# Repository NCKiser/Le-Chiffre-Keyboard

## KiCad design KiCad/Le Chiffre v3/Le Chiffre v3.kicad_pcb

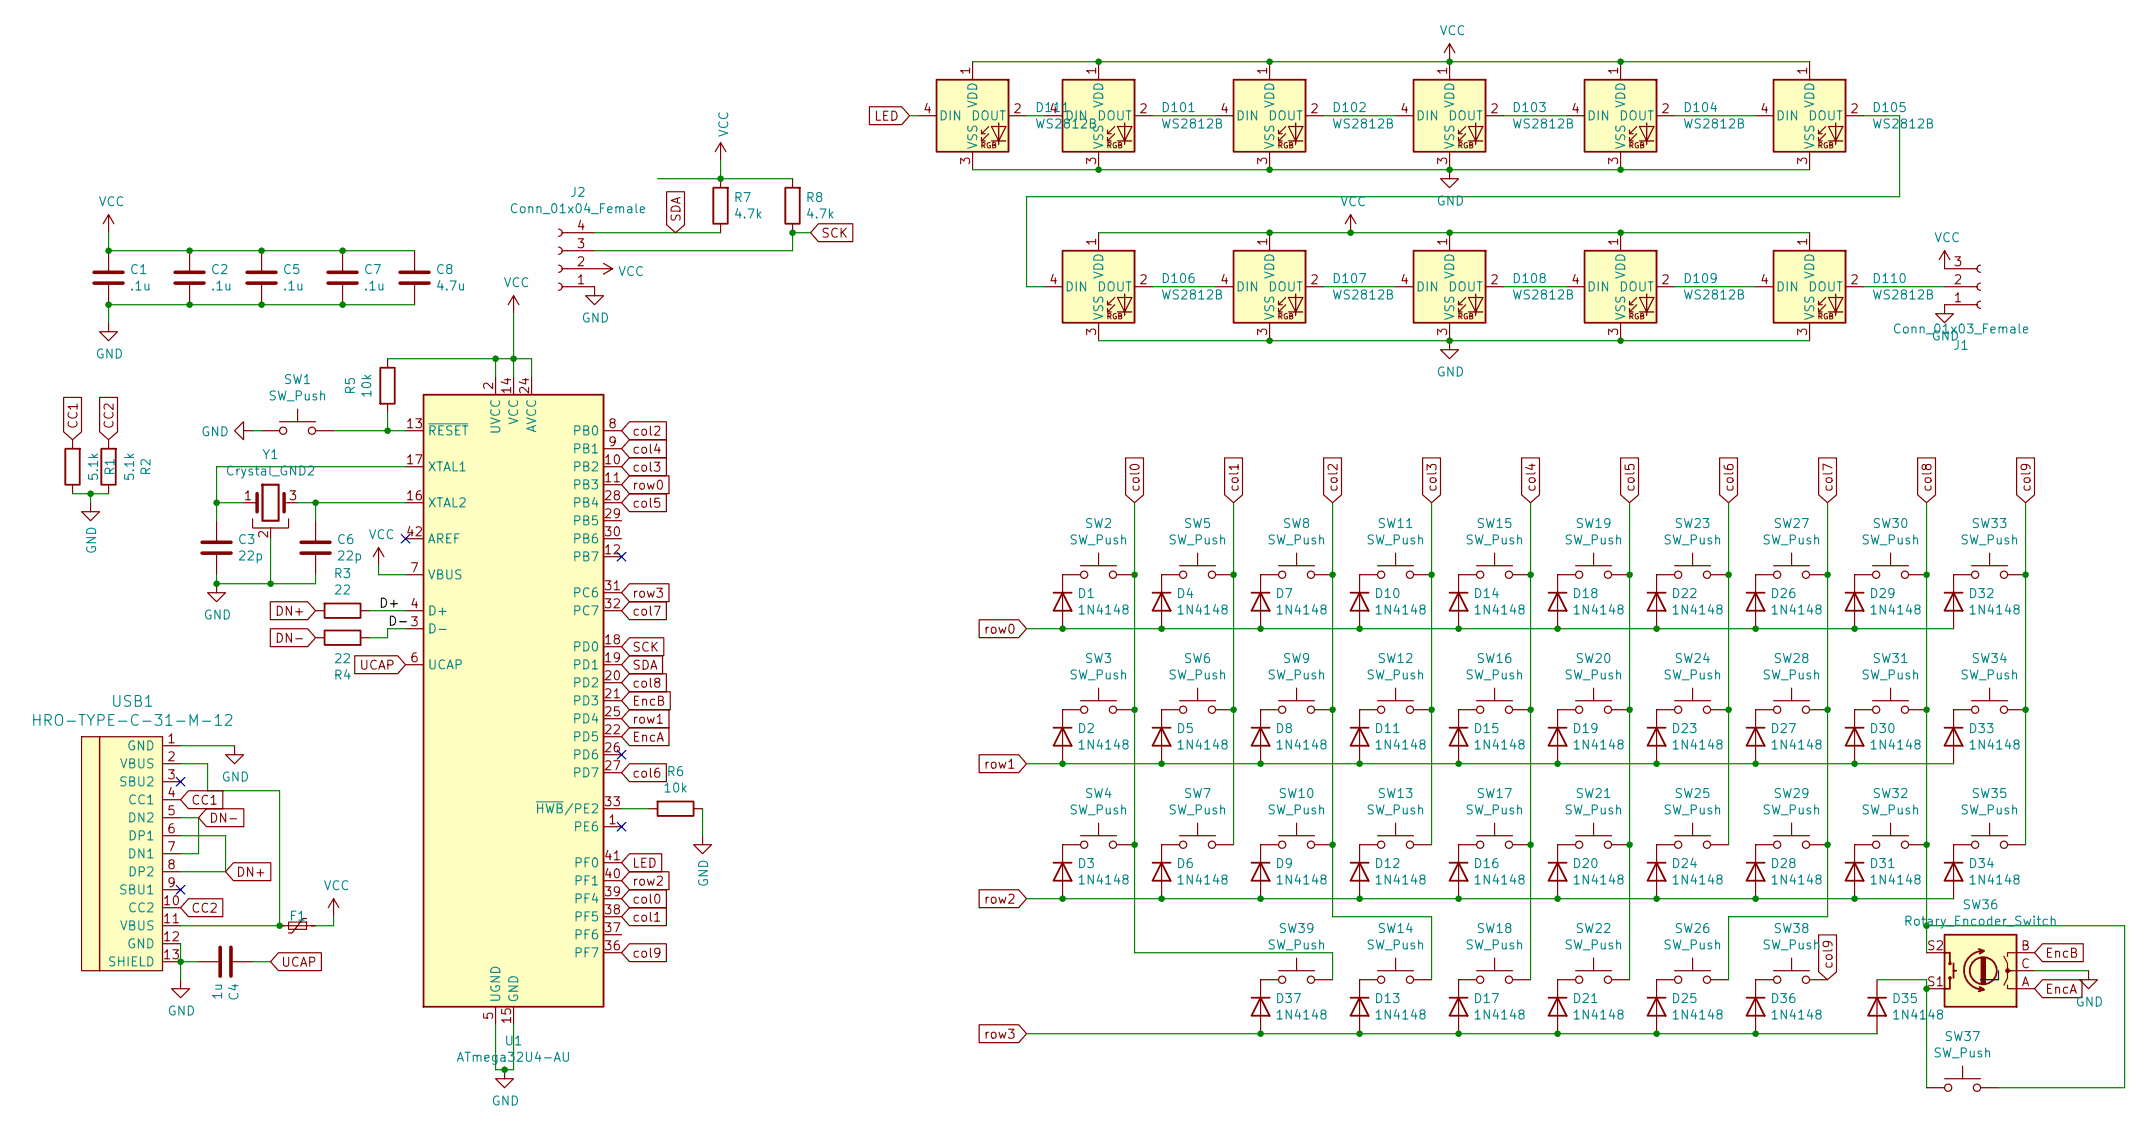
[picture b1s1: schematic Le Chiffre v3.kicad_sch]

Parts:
C1, C2, C5, C7: .1u; C_0603
C3, C6: 22p; C_0603
C4: 1u; C_0603
C8: 4.7u; C_0603
D1, D2, D3, D4, D5, D6, D7, D8, D9, D10, D11, D12, D13, D14, D15, D16, D17, D18, D19, D20, D21, D22, D23, D24, D25, D26, D27, D28, D29, D30, D31, D32, D33, D34, D35, D36, D37: 1N4148; D_SOD123
D101, D102, D103, D104, D105, D106, D107, D108, D109, D110, D111: WS2812B; LED_WS2812B_PLCC4_5.0x5.0mm_P3.2mm
F1: Polyfuse_Small; Fuse_0805
J1: Conn_01x03_Female; PinSocket_1x03_P2.54mm_Vertical
J2: Conn_01x04_Female; PinSocket_1x04_P2.54mm_Vertical
R1, R2: 5.1k; R_0805
R3, R4: 22; R_0805
R5, R6: 10k; R_0805
R7, R8: 4.7k; R_0805
SW1: SW_Push; SW_SPST_TL3342
SW2, SW3, SW4, SW5, SW6, SW7, SW8, SW9, SW10, SW11, SW12, SW13, SW14, SW15, SW16, SW17, SW19, SW20, SW21, SW23, SW24, SW25, SW26, SW27, SW28, SW29, SW30, SW31, SW32, SW33, SW34, SW35, SW37, SW38, SW39: SW_Push; MX-Alps-Choc-1U-NoLED
SW18, SW22: SW_Push; MX-Alps-Choc-2U-StabFlip
SW36: Rotary_Encoder_Switch; RotaryEncoder_Alps_EC12E-Switch_Vertical_H20mm_CircularMoun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
U1: ATmega32U4-AU; ATMEGA32U4-AU
USB1: HRO-TYPE-C-31-M-12; HRO-TYPE-C-31-M-12-HandSoldering
Y1: Crystal_GND2; Crystal_SMD_3225-4pin_3.2x2.5mm

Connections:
/D+: R3.1, U1.4 (D+)
/D-: R4.2, U1.3 (D-)
CC1: R1.2, USB1.4 (CC1)
CC2: R2.2, USB1.10 (CC2)
DN+: R3.2, USB1.6 (DP1), USB1.8 (DP2)
DN-: R4.1, USB1.5 (DN2), USB1.7 (DN1)
EncA: SW36.A, U1.22 (PD5)
EncB: SW36.B, U1.21 (PD3)
GND: C1.2, C2.2, C3.2, C4.2, C5.2, C6.2, C7.2, C8.2, D101.3 (VSS), D102.3 (VSS), D103.3 (VSS), D104.3 (VSS), D105.3 (VSS), D106.3 (VSS), D107.3 (VSS), D108.3 (VSS), D109.3 (VSS), D110.3 (VSS), D111.3 (VSS), J1.1 (Pin_3), J2.1, R1.1, R2.1, R6.1, SW1.1, SW36.C, U1.5 (UGND), U1.15 (GND), U1.23 (GND), U1.35 (GND), U1.43 (GND), USB1.1 (GND), USB1.12 (GND), USB1.13 (SHIELD), Y1.2
LED: D111.4 (DIN), U1.41 (PF0)
unnamed: D1.1 (K), SW2.1
unnamed: D2.1 (K), SW3.1
unnamed: D3.1 (K), SW4.1
unnamed: D4.1 (K), SW5.1
unnamed: D5.1 (K), SW6.1
unnamed: D6.1 (K), SW7.1
unnamed: D7.1 (K), SW8.1
unnamed: D8.1 (K), SW9.1
unnamed: D9.1 (K), SW10.1
unnamed: D10.1 (K), SW11.1
unnamed: D11.1 (K), SW12.1
unnamed: D12.1 (K), SW13.1
unnamed: D13.1 (K), SW14.1
unnamed: D14.1 (K), SW15.1
unnamed: D15.1 (K), SW16.1
unnamed: D16.1 (K), SW17.1
unnamed: D17.1 (K), SW18.1
unnamed: D18.1 (K), SW19.1
unnamed: D19.1 (K), SW20.1
unnamed: D20.1 (K), SW21.1
unnamed: D21.1 (K), SW22.1
unnamed: D22.1 (K), SW23.1
unnamed: D23.1 (K), SW24.1
unnamed: D24.1 (K), SW25.1
unnamed: D25.1 (K), SW26.1
unnamed: D26.1 (K), SW27.1
unnamed: D27.1 (K), SW28.1
unnamed: D28.1 (K), SW29.1
unnamed: D29.1 (K), SW30.1
unnamed: D30.1 (K), SW31.1
unnamed: D31.1 (K), SW32.1
unnamed: D32.1 (K), SW33.1
unnamed: D33.1 (K), SW34.1
unnamed: D34.1 (K), SW35.1
unnamed: D35.1 (K), SW36.S1, SW37.1
unnamed: D36.1 (K), SW38.1
unnamed: D37.1 (K), SW39.1
unnamed: D101.4 (DIN), D111.2 (DOUT)
unnamed: D101.2 (DOUT), D102.4 (DIN)
unnamed: D102.2 (DOUT), D103.4 (DIN)
unnamed: D103.2 (DOUT), D104.4 (DIN)
unnamed: D104.2 (DOUT), D105.4 (DIN)
unnamed: D105.2 (DOUT), D106.4 (DIN)
unnamed: D106.2 (DOUT), D107.4 (DIN)
unnamed: D107.2 (DOUT), D108.4 (DIN)
unnamed: D108.2 (DOUT), D109.4 (DIN)
unnamed: D109.2 (DOUT), D110.4 (DIN)
unnamed: D110.2 (DOUT), J1.2
unnamed: F1.2, USB1.2 (VBUS), USB1.11 (VBUS)
unnamed: C3.1, U1.17 (XTAL1), Y1.1
unnamed: C6.1, U1.16 (XTAL2), Y1.3
unnamed: R6.2, U1.33 (~HWB/PE2)
unnamed: R5.2, SW1.2, U1.13 (~RESET)
SCK: J2.3, R8.1, U1.18 (PD0)
SDA: J2.4, R7.1, U1.19 (PD1)
UCAP: C4.1, U1.6 (UCAP)
VCC: C1.1, C2.1, C5.1, C7.1, C8.1, D101.1 (VDD), D102.1 (VDD), D103.1 (VDD), D104.1 (VDD), D105.1 (VDD), D106.1 (VDD), D107.1 (VDD), D108.1 (VDD), D109.1 (VDD), D110.1 (VDD), D111.1 (VDD), F1.1, J1.3 (Pin_1), J2.2, R5.1, R7.2, R8.2, U1.2 (UVCC), U1.7 (VBUS), U1.14 (VCC), U1.24 (AVCC), U1.34 (VCC), U1.44 (AVCC)
col0: SW2.2, SW3.2, SW4.2, SW39.2, U1.39 (PF4)
col1: SW5.2, SW6.2, SW7.2, U1.38 (PF5)
col2: SW8.2, SW9.2, SW10.2, SW14.2, U1.8 (PB0)
col3: SW11.2, SW12.2, SW13.2, U1.10 (PB2)
col4: SW15.2, SW16.2, SW17.2, SW18.2, U1.9 (PB1)
col5: SW19.2, SW20.2, SW21.2, SW22.2, U1.28 (PB4)
col6: SW23.2, SW24.2, SW25.2, U1.27 (PD7)
col7: SW26.2, SW27.2, SW28.2, SW29.2, U1.32 (PC7)
col8: SW30.2, SW31.2, SW32.2, SW36.S2, SW37.2, U1.20 (PD2)
col9: SW33.2, SW34.2, SW35.2, SW38.2, U1.36 (PF7)
row0: D1.2 (A), D4.2 (A), D7.2 (A), D10.2 (A), D14.2 (A), D18.2 (A), D22.2 (A), D26.2 (A), D29.2 (A), D32.2 (A), U1.11 (PB3)
row1: D2.2 (A), D5.2 (A), D8.2 (A), D11.2 (A), D15.2 (A), D19.2 (A), D23.2 (A), D27.2 (A), D30.2 (A), D33.2 (A), U1.25 (PD4)
row2: D3.2 (A), D6.2 (A), D9.2 (A), D12.2 (A), D16.2 (A), D20.2 (A), D24.2 (A), D28.2 (A), D31.2 (A), D34.2 (A), U1.40 (PF1)
row3: D13.2 (A), D17.2 (A), D21.2 (A), D25.2 (A), D35.2 (A), D36.2 (A), D37.2 (A), U1.31 (PC6)

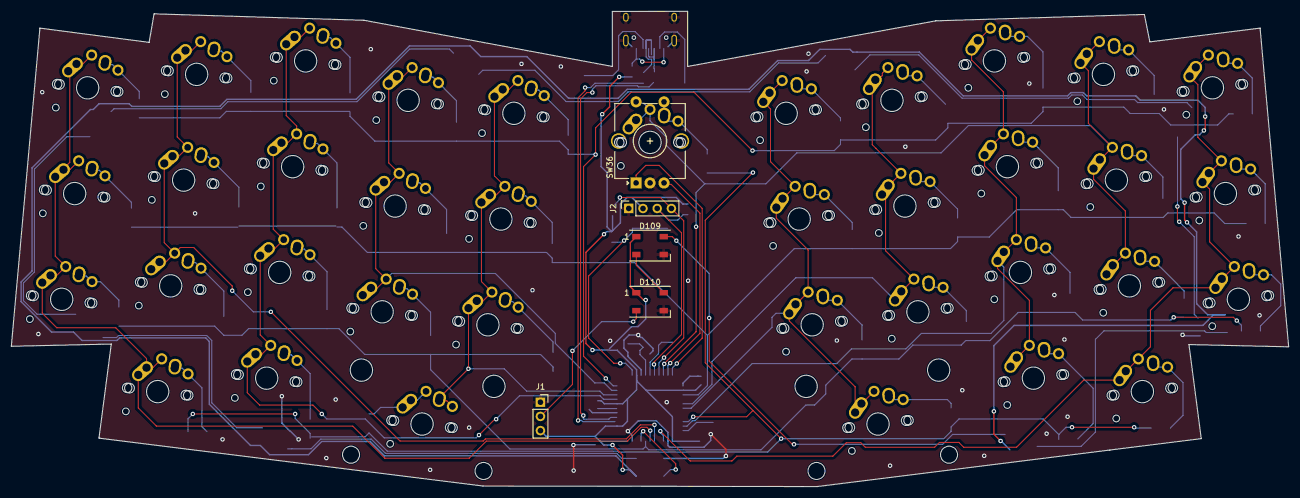
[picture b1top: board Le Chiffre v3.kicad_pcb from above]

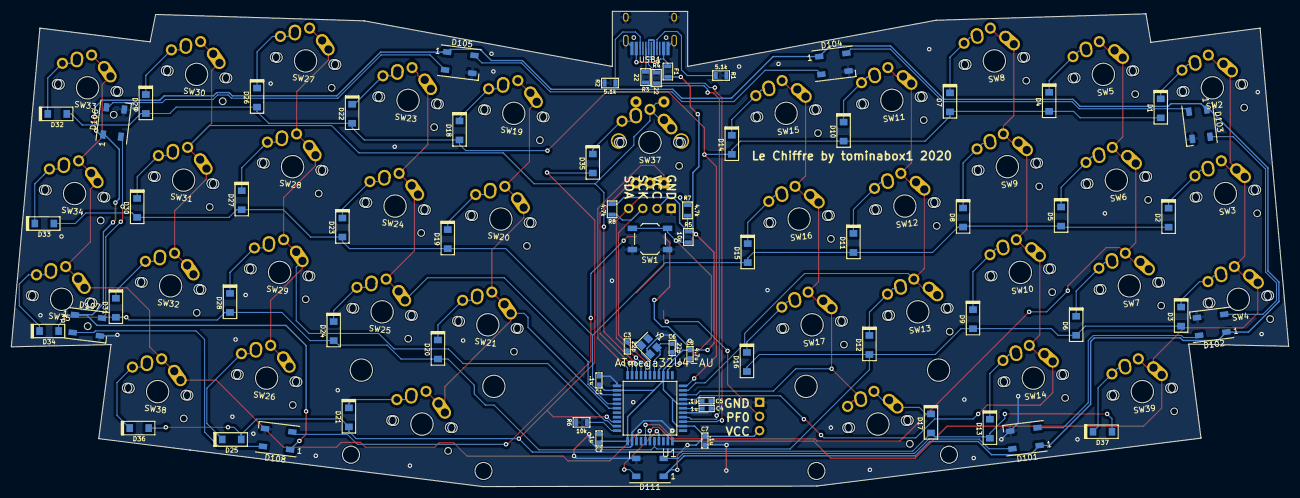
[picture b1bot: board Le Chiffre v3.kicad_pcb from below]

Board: 2 copper layers, 228.4 x 85.0 mm, 109 parts (67 on the bottom side), 81 nets.

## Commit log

2023-10-20 Add V3
    Adds an iteration on the V2 board by replacing the 1.25u keys with two 1u keys in line with their respective physical columns, and wired to the outermost electrical columns. Board outline updated to 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
